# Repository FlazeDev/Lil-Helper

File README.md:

# LIL HELPER
A macropad with 12 keys and an encoder. I used Kicad, onshape and kmk to make it.  
OVERALL HACKPAD

# INSPIRATION
I do video editing, 3d modelling, making games, music, and studying too. So, I needed something that could increase my efficiency, and here it is, my lil helper.

# CAD
I made the CAD using onshape(too dumb to learn freecad and my pc didnt have enough space for fusion in my c drive). Took me waayy too long, but its done.  CAD

# PCB
Made the PCB using Kicad, the wiring is horrendous but it works.  
SCHEMATIC

PCB  

# FIRMWARE
I used kmk to make firmware since im already familiar with python.  

# BOM
12x Cherry MX Switches  
1x Xiao RP2040  
1x EC11 Rotary encoder  
16x Through-hole 1N4148 Diodes  
4x M3x16mm screws  
4x M3x5mx4mm heatset inserts

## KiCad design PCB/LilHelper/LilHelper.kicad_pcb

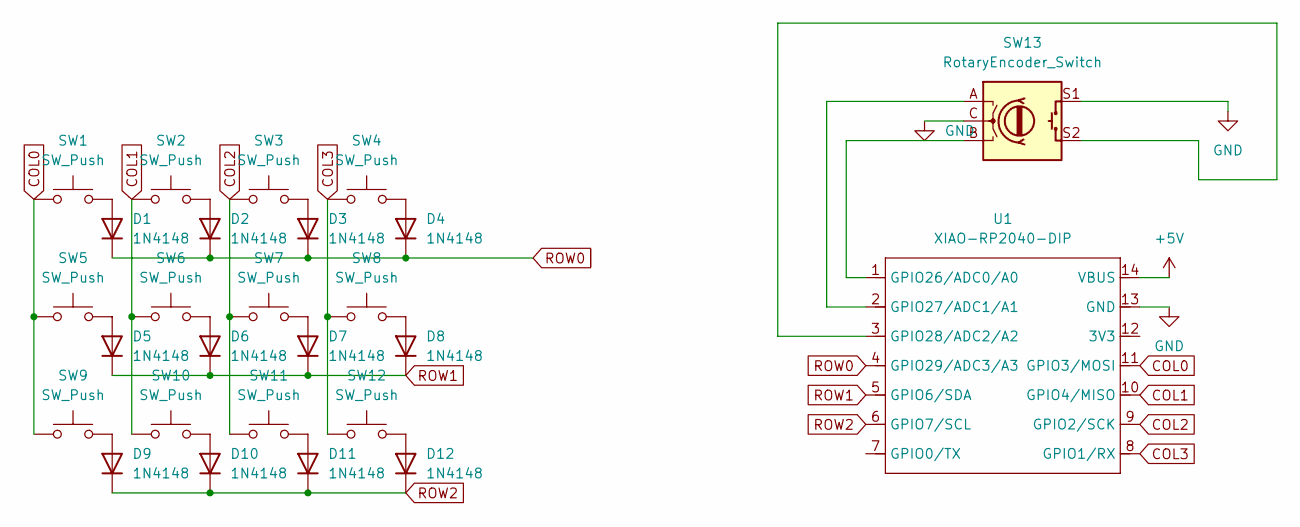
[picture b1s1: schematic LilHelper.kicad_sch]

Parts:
D1, D2, D3, D4, D5, D6, D7, D8, D9, D10, D11, D12: 1N4148; D_DO-35_SOD27_P7.62mm_Horizontal
SW1, SW2, SW3, SW4, SW5, SW6, SW7, SW8, SW9, SW10, SW11, SW12: SW_Push; SW_Cherry_MX_1.00u_PCB
SW13: RotaryEncoder_Switch; RotaryEncoder_Alps_EC11E-Switch_Vertical_H20mm
U1: XIAO-RP2040-DIP

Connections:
+5V: U1.14 (VBUS)
COL0: SW1.1, SW5.1, SW9.1, U1.11 (GPIO3/MOSI)
COL1: SW2.1, SW6.1, SW10.1, U1.10 (GPIO4/MISO)
COL2: SW3.1, SW7.1, SW11.1, U1.9 (GPIO2/SCK)
COL3: SW4.1, SW8.1, SW12.1, U1.8 (GPIO1/RX)
GND: SW13.C, SW13.S1, U1.13 (GND)
unnamed: D1.2 (A), SW1.2
unnamed: D2.2 (A), SW2.2
unnamed: D3.2 (A), SW3.2
unnamed: D4.2 (A), SW4.2
unnamed: D5.2 (A), SW5.2
unnamed: D6.2 (A), SW6.2
unnamed: D7.2 (A), SW7.2
unnamed: D8.2 (A), SW8.2
unnamed: D9.2 (A), SW9.2
unnamed: D10.2 (A), SW10.2
unnamed: D11.2 (A), SW11.2
unnamed: D12.2 (A), SW12.2
unnamed: SW13.B, U1.1 (GPIO26/ADC0/A0)
unnamed: SW13.A, U1.2 (GPIO27/ADC1/A1)
unnamed: SW13.S2, U1.3 (GPIO28/ADC2/A2)
ROW0: D1.1 (K), D2.1 (K), D3.1 (K), D4.1 (K), U1.4 (GPIO29/ADC3/A3)
ROW1: D5.1 (K), D6.1 (K), D7.1 (K), D8.1 (K), U1.5 (GPIO6/SDA)
ROW2: D9.1 (K), D10.1 (K), D11.1 (K), D12.1 (K), U1.6 (GPIO7/SCL)

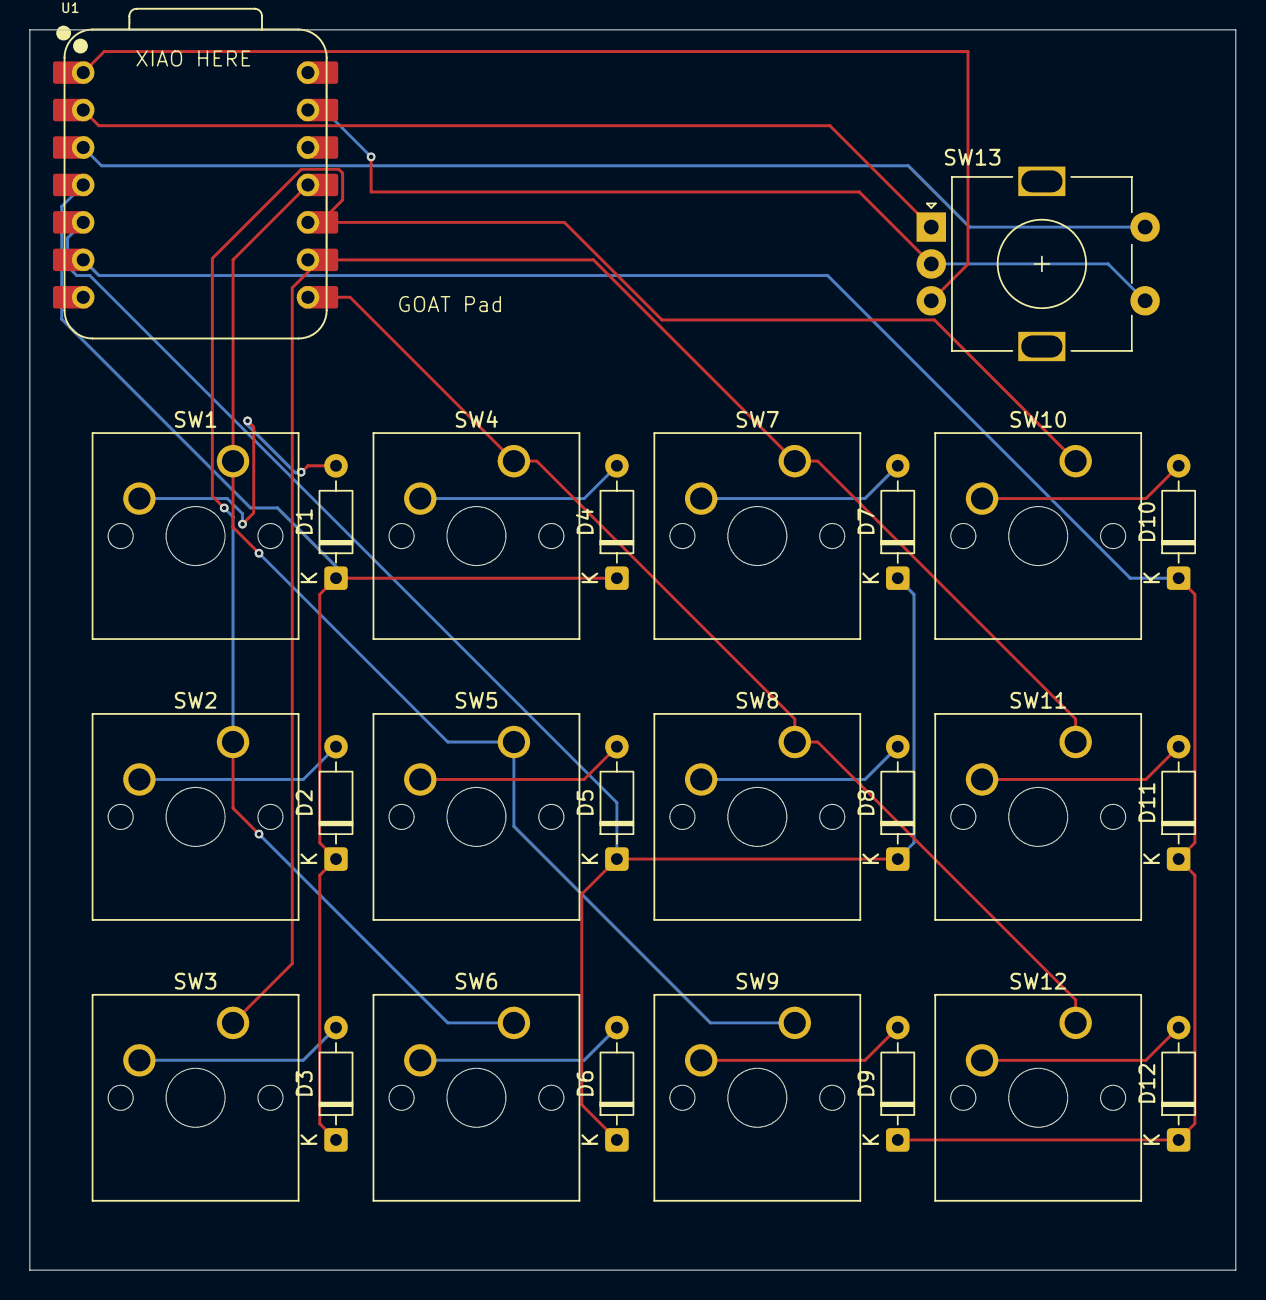
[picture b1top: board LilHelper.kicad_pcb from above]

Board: 2 copper layers, 81.8 x 84.1 mm, 26 parts (0 on the bottom side), 23 nets.

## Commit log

2025-12-10 firmware created
2025-12-10 Final Commit(Hopefully)
2025-12-10 FINAL COMMIT
2025-12-11 Just some extras for easy access
